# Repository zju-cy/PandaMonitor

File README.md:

# PandaMonitor
A monitor build by raspberry-pi for my baby.

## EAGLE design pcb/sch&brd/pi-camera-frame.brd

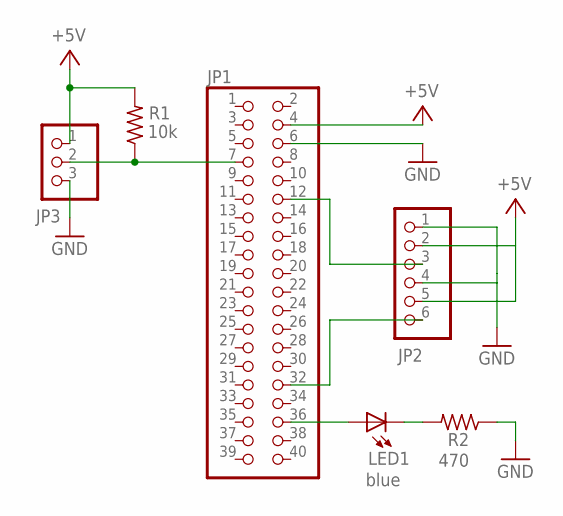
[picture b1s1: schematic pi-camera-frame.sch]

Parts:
JP1: PINHD-2X20; 2X20
JP2: PINHD-1X6; 1X06
JP3: PINHD-1X3; 1X03
LED1: blue; CHIP-LED0603
R1: 10k; R0805
R2: 470; R0805

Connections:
+5V: JP1.4, JP2.2, JP2.5, JP3.1, R1.2
GND: JP1.6, JP2.1, JP2.4, JP3.3, R2.1
unnamed: JP1.12, JP2.3
unnamed: JP1.7, JP3.2, R1.1
unnamed: JP1.36, LED1.A
unnamed: JP1.32, JP2.6
unnamed: LED1.C, R2.2

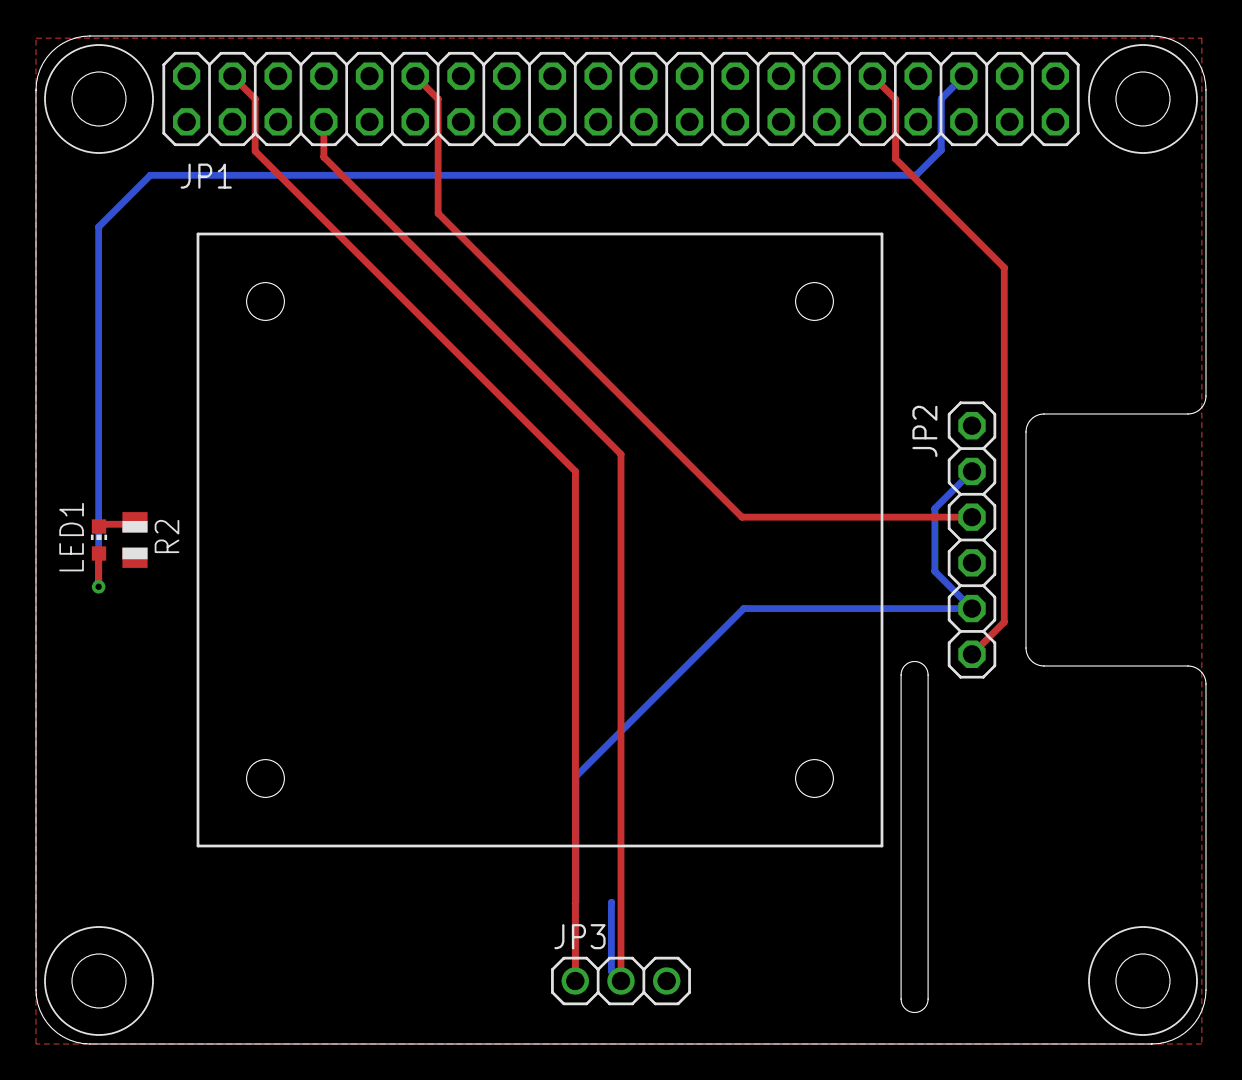
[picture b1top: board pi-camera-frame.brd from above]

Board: 2 copper layers, 65.0 x 56.0 mm, 6 parts (1 on the bottom side), 7 nets.

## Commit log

2019-05-12 init
2019-05-25 update index, add pi's info.
2019-05-25 add database for sensor data
2019-05-26 add breath led to indicate system is running.
2019-05-26 add database file
